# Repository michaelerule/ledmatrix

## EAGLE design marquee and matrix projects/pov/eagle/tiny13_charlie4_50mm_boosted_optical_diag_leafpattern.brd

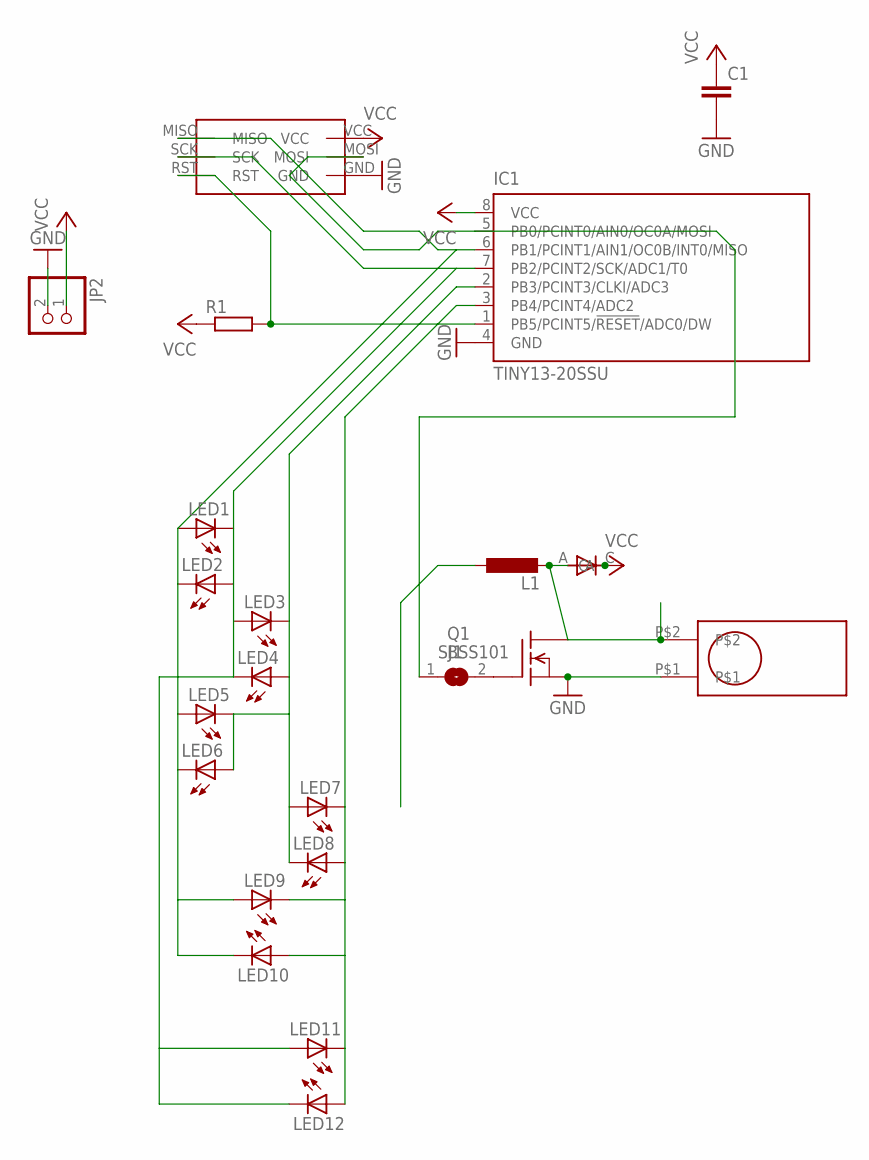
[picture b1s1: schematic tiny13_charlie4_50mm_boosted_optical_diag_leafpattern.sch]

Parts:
C1: C-EU025-025X050; C025-025X050
IC1: TINY13-20SSU; 8S1
JP2: PINHD-1X2; 1X02
L1: L-EU0204/5; 0204/5
LED1, LED2, LED3, LED4, LED5, LED6, LED7, LED8, LED9, LED10, LED11, LED12: LED3MM
Q1: BSS101; TO92
R1: R-EU_0204/5; 0204/5
SJ1: SJ
U$1: TILT_SWITCH_MECHANICAL
U$2: AVR_ISP_6_PIN_1X6_SMT_CONTACT_PROGRAMMER; CONTACT_ISP_PROGRAMMER_1X6_ATMEL_2
U$3: D-6; D-7.5

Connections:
GND: C1.2, IC1.4 (GND), JP2.2, Q1.1 (S), U$1.P$1, U$2.GND
unnamed: IC1.2 (PB3/PCINT3/CLKI/ADC3), LED3.K (C), LED4.A, LED5.K (C), LED6.A, LED7.A, LED8.K (C)
unnamed: IC1.7 (PB2/PCINT2/SCK/ADC1/T0), LED1.K (C), LED2.A, LED3.A, LED4.K (C), LED11.A, LED12.K (C), U$2.SCK
unnamed: L1.2, Q1.3 (D), U$1.P$2, U$3.A
unnamed: IC1.3 (PB4/PCINT4/ADC2), LED7.K (C), LED8.A, LED9.K (C), LED10.A, LED11.K (C), LED12.A
unnamed: IC1.5 (PB0/PCINT0/AIN0/OC0A/MOSI), SJ1.1, U$2.MOSI
unnamed: IC1.1 (PB5/PCINT5/!RESET!/ADC0/DW), R1.2, U$2.RST
unnamed: IC1.6 (PB1/PCINT1/AIN1/OC0B/INT0/MISO), LED1.A, LED2.K (C), LED5.A, LED6.K (C), LED9.A, LED10.K (C), U$2.MISO
unnamed: Q1.2 (G), SJ1.2
VCC: C1.1, IC1.8 (VCC), JP2.1, R1.1, U$2.VCC, U$3.C

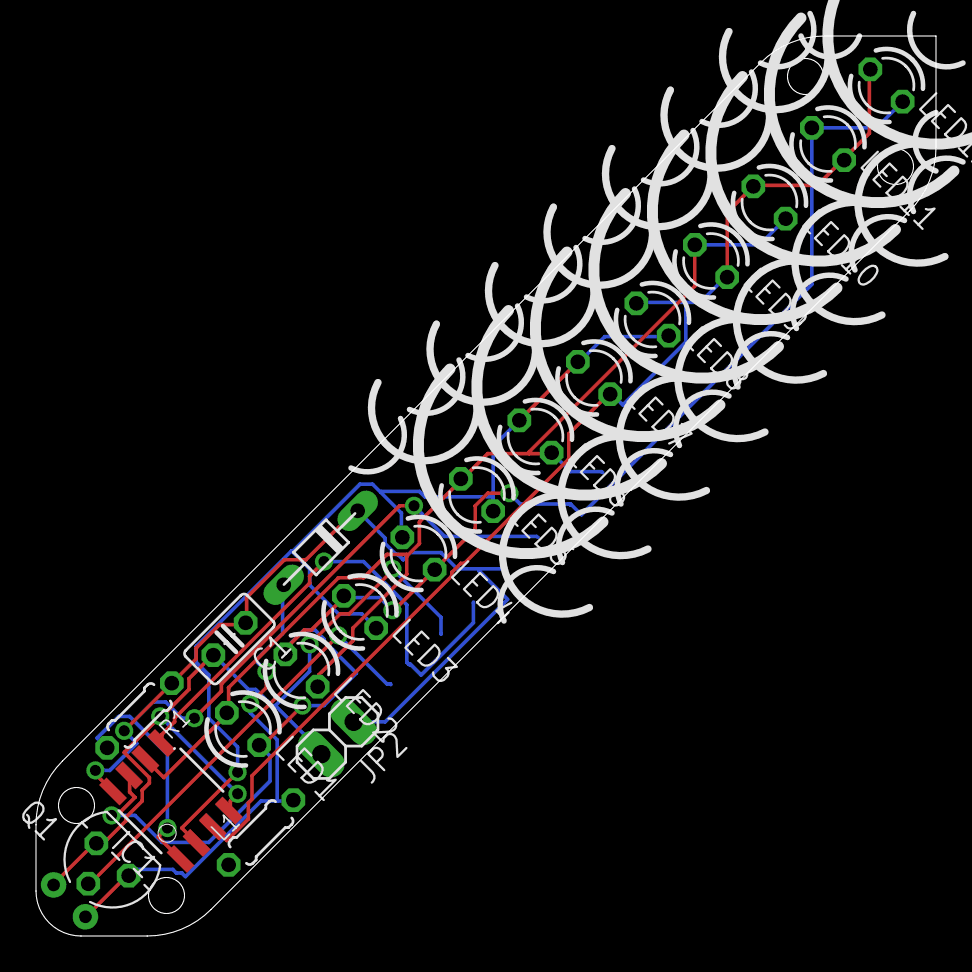
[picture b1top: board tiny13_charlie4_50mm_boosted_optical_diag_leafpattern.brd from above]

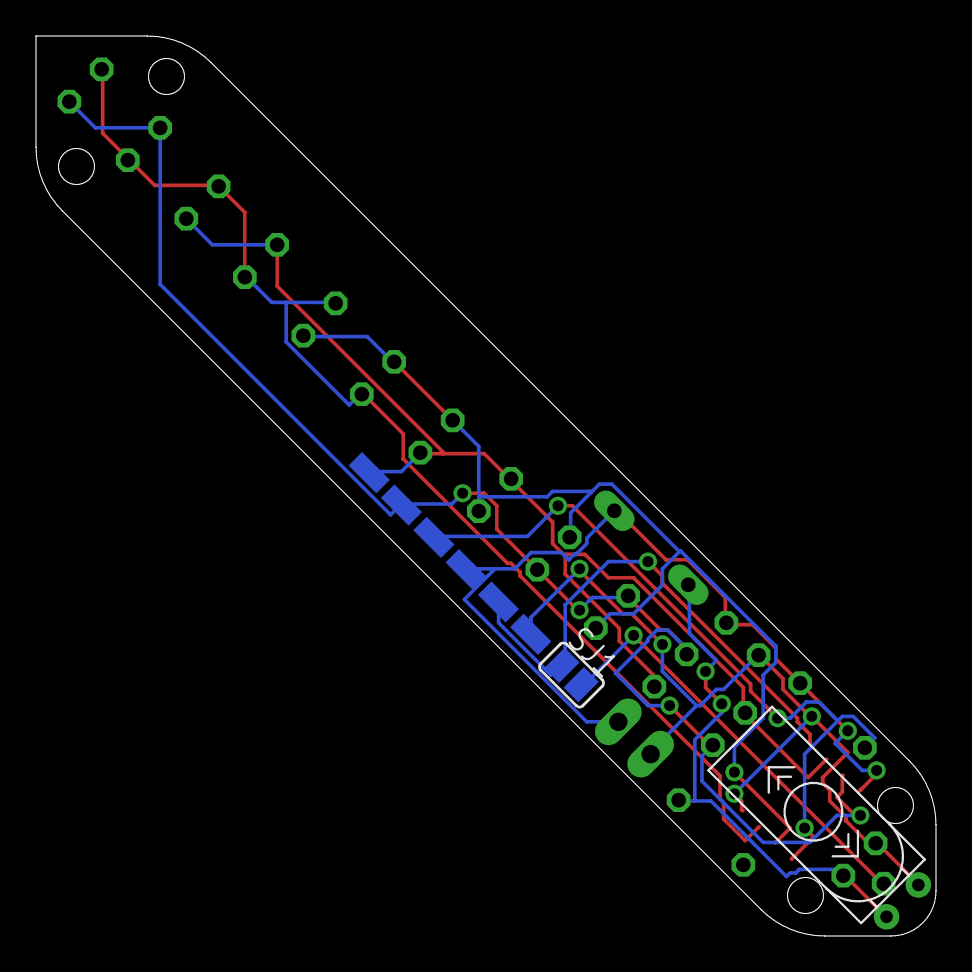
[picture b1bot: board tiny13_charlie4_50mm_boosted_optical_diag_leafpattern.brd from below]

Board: 2 copper layers, 50.0 x 50.0 mm, 22 parts (3 on the bottom side), 10 nets.

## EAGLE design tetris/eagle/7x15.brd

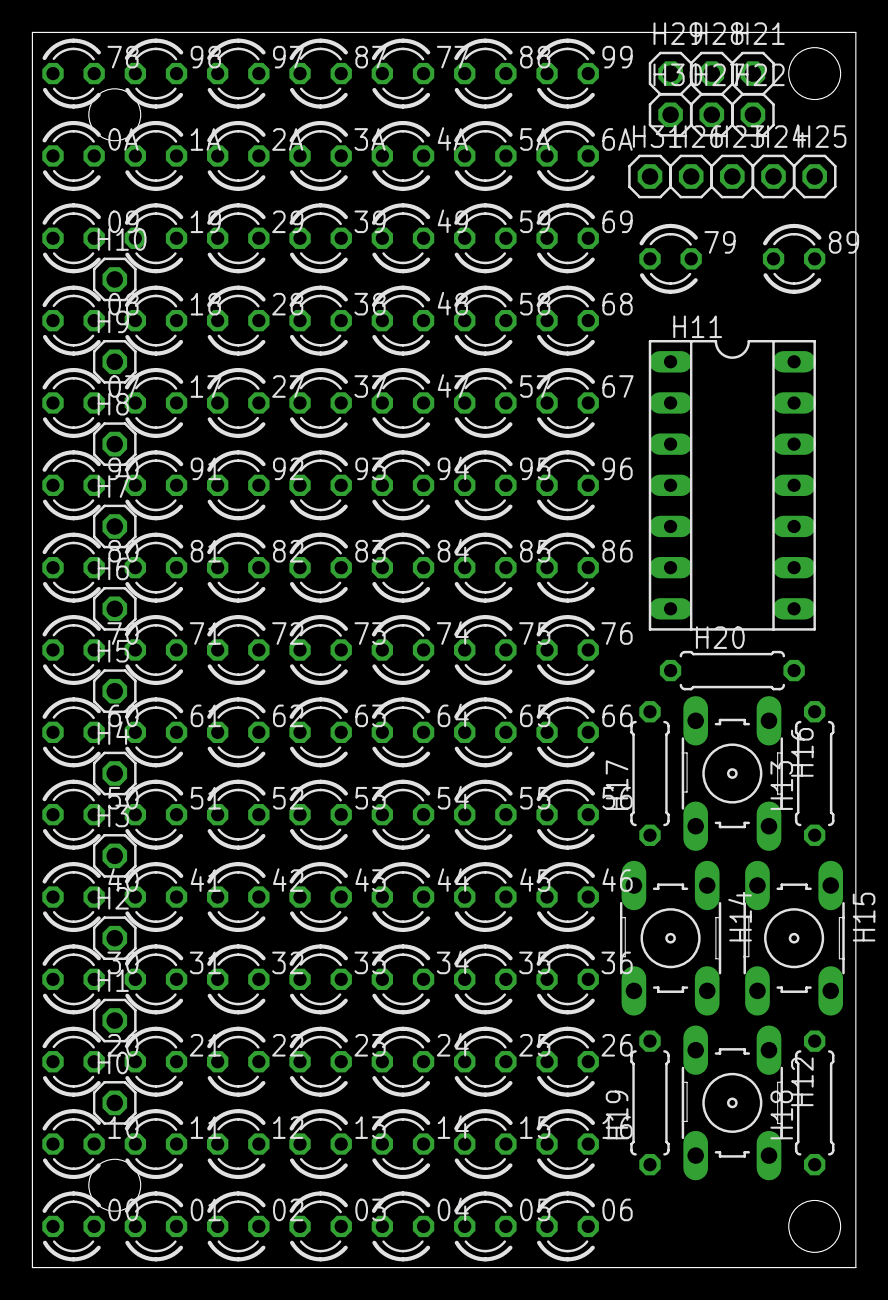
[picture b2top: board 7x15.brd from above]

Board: 2 copper layers, 50.8 x 76.2 mm, 139 parts (0 on the bottom side), 11 nets, no tracks yet.

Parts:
00, 0A, 01, 1A, 02, 2A, 03, 3A, 04, 4A, 05, 5A, 06, 6A, 07, 08, 09, 10, 11, 12, 13, 14, 15, 16, 17, 18, 19, 20, 21, 22, 23, 24, 25, 26, 27, 28, 29, 30, 31, 32, 33, 34, 35, 36, 37, 38, 39, 40, 41, 42, 43, 44, 45, 46, 47, 48, 49, 50, 51, 52, 53, 54, 55, 56, 57, 58, 59, 60, 61, 62, 63, 64, 65, 66, 67, 68, 69, 70, 71, 72, 73, 74, 75, 76, 77, 78, 79, 80, 81, 82, 83, 84, 85, 86, 87, 88, 89, 90, 91, 92, 93, 94, 95, 96, 97, 98, 99: LED3MM
H0, H1, H2, H3, H4, H5, H6, H7, H8, H9, H10, H21, H22, H23, H24, H25, H26, H27, H28, H29, H30, H31: 1X01
H11: SOCKET-14
H12, H14, H15, H16: B3F-10XX
H13, H17, H18, H19, H20: 0207/7

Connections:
D: 00.A, 0A.K, 1A.K, 2A.K, 3A.K, 4A.K, 5A.K, 6A.K, 11.A, 22.A, 33.A, 44.A, 55.A, 66.A, 77.A, 88.A, 99.A, H10.1
S0: 00.K, 0A.A, 01.A, 02.A, 03.A, 04.A, 05.A, 06.A, 07.A, 08.A, 09.A, 10.K, 20.K, 30.K, 40.K, 50.K, 60.K, 70.K, 80.K, 90.K, H0.1
S1: 01.K, 1A.A, 10.A, 11.K, 12.A, 13.A, 14.A, 15.A, 16.A, 17.A, 18.A, 19.A, 21.K, 31.K, 41.K, 51.K, 61.K, 71.K, 81.K, 91.K, H1.1
S2: 02.K, 2A.A, 12.K, 20.A, 21.A, 22.K, 23.A, 24.A, 25.A, 26.A, 27.A, 28.A, 29.A, 32.K, 42.K, 52.K, 62.K, 72.K, 82.K, 92.K, H2.1
S3: 03.K, 3A.A, 13.K, 23.K, 30.A, 31.A, 32.A, 33.K, 34.A, 35.A, 36.A, 37.A, 38.A, 39.A, 43.K, 53.K, 63.K, 73.K, 83.K, 93.K, H3.1
S4: 04.K, 4A.A, 14.K, 24.K, 34.K, 40.A, 41.A, 42.A, 43.A, 44.K, 45.A, 46.A, 47.A, 48.A, 49.A, 54.K, 64.K, 74.K, 84.K, 94.K, H4.1
S5: 05.K, 5A.A, 15.K, 25.K, 35.K, 45.K, 50.A, 51.A, 52.A, 53.A, 54.A, 55.K, 56.A, 57.A, 58.A, 59.A, 65.K, 75.K, 85.K, 95.K, H5.1
S6: 06.K, 6A.A, 16.K, 26.K, 36.K, 46.K, 56.K, 60.A, 61.A, 62.A, 63.A, 64.A, 65.A, 66.K, 67.A, 68.A, 69.A, 76.K, 86.K, 96.K, H6.1
S7: 07.K, 17.K, 27.K, 37.K, 47.K, 57.K, 67.K, 70.A, 71.A, 72.A, 73.A, 74.A, 75.A, 76.A, 77.K, 78.A, 87.K, 97.K, H7.1
S8: 08.K, 18.K, 28.K, 38.K, 48.K, 58.K, 68.K, 78.K, 80.A, 81.A, 82.A, 83.A, 84.A, 85.A, 86.A, 87.A, 88.K, 98.K, H8.1
S9: 09.K, 19.K, 29.K, 39.K, 49.K, 59.K, 69.K, 90.A, 91.A, 92.A, 93.A, 94.A, 95.A, 96.A, 97.A, 98.A, 99.K, H9.1

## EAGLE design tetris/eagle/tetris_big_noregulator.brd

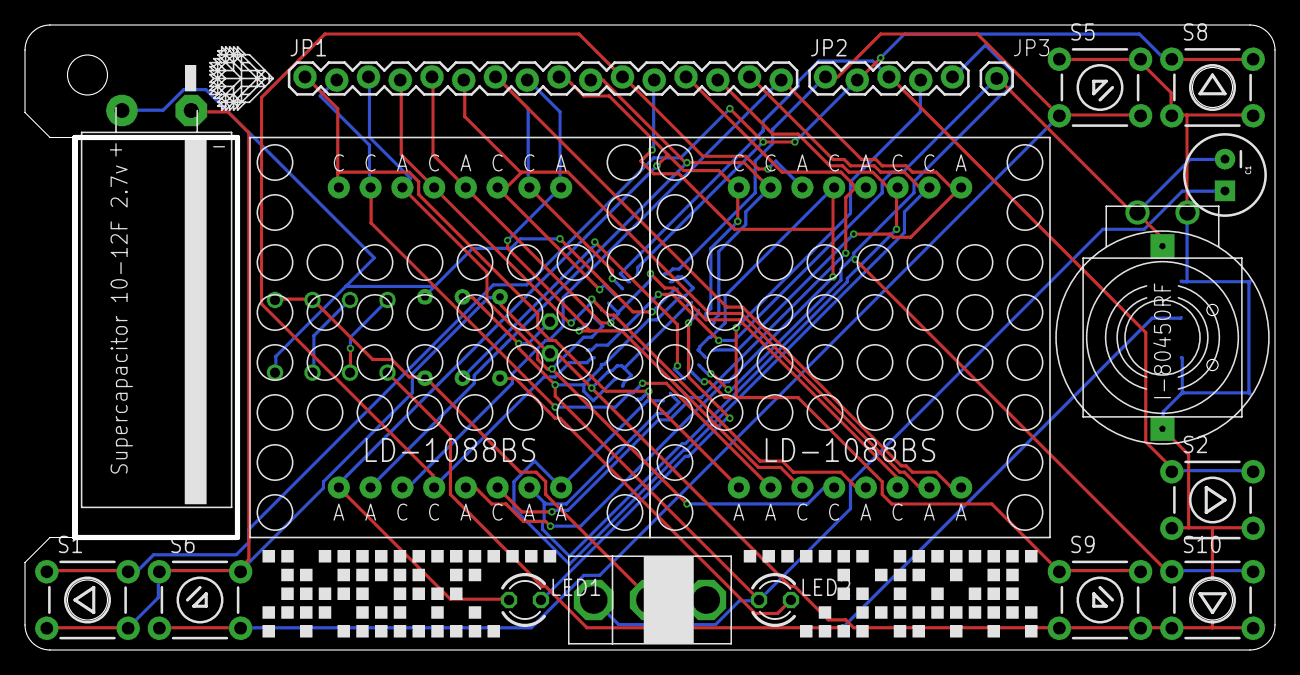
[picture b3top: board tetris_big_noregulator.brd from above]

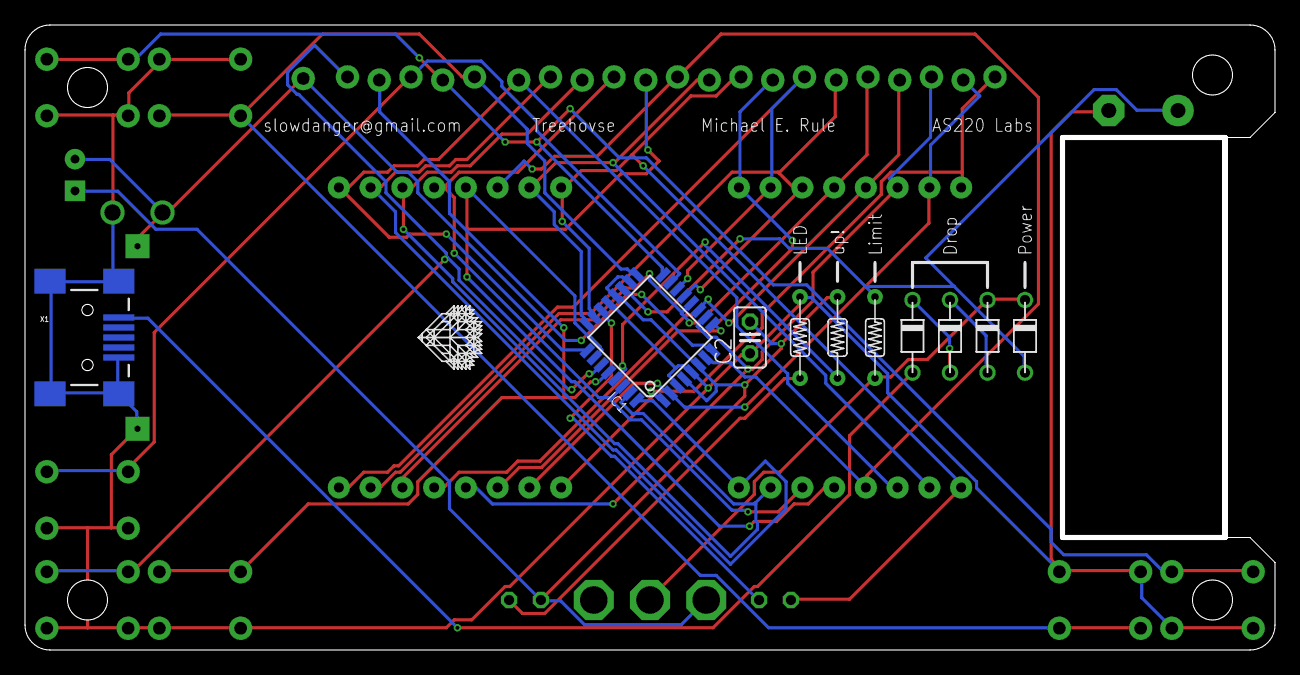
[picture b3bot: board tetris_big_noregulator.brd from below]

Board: 2 copper layers, 100.0 x 50.0 mm, 31 parts (11 on the bottom side), 32 nets.

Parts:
C1: CPOL-RADIAL-100UF-25V
C2: C025-025X050
IC1: MEGA8-AI; TQFP32-08
JP1: M16LOCK; 1X16_LOCK
JP2: 1X05_LOCK
JP3: M01PTH; 1X01
LED1, LED2: LED3MM
S1, S2, S5, S6, S8, S9, S10: TACTILE-PTH
U$1, U$2: LD-1088BS
U$3, U$6: LOGO
U$4: I-80450RF; ISK4.1K_I-80450RF_I2G
U$5: NICHICON_12F; NICHICON_10X30
U$7: PIEZO_ROUND_PTH; PIEZO_ROUND_ENCASED_PTH
U$8, U$10, U$11: R-7
U$9: SPST_BIG_PTH; SWITCH_BIG
U$13, U$14, U$15, U$16: D-6; D-7.5
X1: USB-MINIB-5PIN; USB-MINIB

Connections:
GND: C2.1, IC1.3, IC1.5, IC1.21, S1.3, S1.4, S2.3, S2.4, S5.1, S5.2, S6.1, S6.2, S8.3, S8.4, S9.3, S9.4, S10.3, S10.4, U$4.P$2, U$5.P$1, U$7.P$2, U$11.P$2, X1.GND, X1.MTN1, X1.MTN2, X1.MTN3, X1.MTN4
unnamed: IC1.32, JP1.15, U$1.A4, U$2.C1
unnamed: IC1.31, JP1.14, U$1.A5, U$2.C2
unnamed: IC1.30, JP1.13, U$1.C6, U$2.A2
unnamed: IC1.26, JP1.12, U$1.A6, U$2.C3
unnamed: IC1.7, JP1.11, U$1.C7, U$2.A3
unnamed: IC1.24, JP1.10, U$1.A7, U$2.C4
unnamed: IC1.23, JP1.9, LED1.A, U$1.A8, U$2.C5
unnamed: IC1.25, JP1.16, U$1.C8, U$2.A1
unnamed: U$15.A, X1.VBUS
unnamed: IC1.13, JP1.6, U$1.C2, U$2.A5
unnamed: IC1.12, JP1.5, U$1.A2, U$2.C6
unnamed: IC1.11, JP1.4, U$1.C3, U$2.A6
unnamed: IC1.10, JP1.3, U$1.A3, U$2.C7
unnamed: IC1.9, JP1.8, U$1.A1, U$2.C8
unnamed: IC1.2, JP1.2, U$1.C4, U$2.A7
unnamed: IC1.1, JP1.1, U$1.C5, U$2.A8
unnamed: C1.2, IC1.8, JP3.1, U$4.P$1, U$7.P$1
unnamed: U$14.A, U$15.C
unnamed: IC1.29, U$10.P$1
unnamed: IC1.27, JP2.5, S10.1, S10.2
unnamed: IC1.28, JP2.4, S9.1, S9.2
unnamed: IC1.15, JP2.3, S2.1, S2.2
unnamed: IC1.16, JP2.2, S1.1, S1.2, S8.1, S8.2
unnamed: U$8.P$2, U$9.P$2, U$13.C, U$16.C
unnamed: IC1.19, U$5.P$2, U$8.P$1, U$16.A
unnamed: IC1.17, JP2.1, S5.3, S5.4, S6.3, S6.4
unnamed: U$13.A, U$14.C
unnamed: IC1.14, JP1.7, U$1.C1, U$2.A4
unnamed: LED2.K, U$11.P$1
unnamed: IC1.22, LED1.K
VCC: C1.1, C2.2, IC1.4, IC1.6, IC1.18, IC1.20, LED2.A, U$9.P$1, U$10.P$2

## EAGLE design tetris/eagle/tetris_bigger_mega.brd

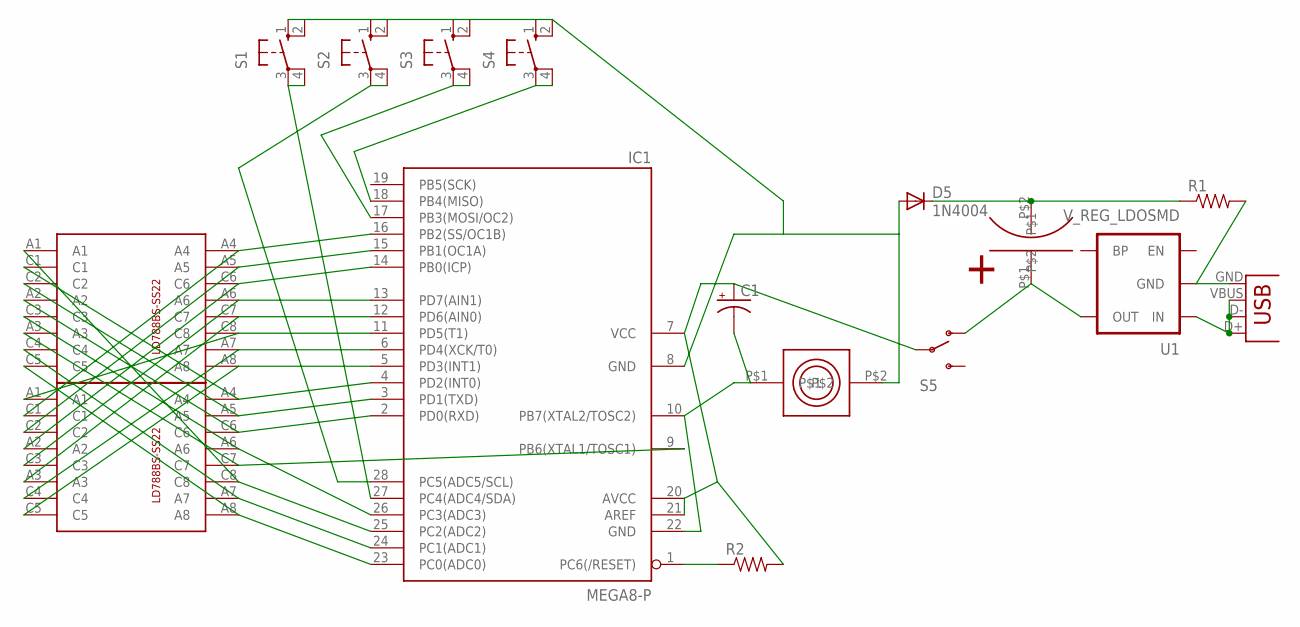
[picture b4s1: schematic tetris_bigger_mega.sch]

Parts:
C1: CAP_POLPTH1; CPOL-RADIAL-100UF-25V
D5: 1N4004; DO41-10
IC1: MEGA8-P; DIL28-3
R1, R2: RESISTORPTH1; AXIAL-0.3
S1, S2, S3, S4: 10-XX; B3F-10XX
S5: SWITCH-SPSTSMD2; SWITCH-SPDT-SMD
U1: V_REG_LDOSMD; SOT23-5
U$1, U$2: LD-1088BS
U$4: I-80450RF; ISK4.1K_I-80450RF_I2G
U$5: NICHICON_12F; NICHICON_10X30
X1: USB-MICROB

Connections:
unnamed: IC1.4 (PD2(INT0)), U$1.A4, U$2.C1
unnamed: IC1.3 (PD1(TXD)), U$1.A5, U$2.C2
unnamed: IC1.2 (PD0(RXD)), U$1.C6, U$2.A2
unnamed: IC1.26 (PC3(ADC3)), U$1.A6, U$2.C3
unnamed: IC1.9 (PB6(XTAL1/TOSC1)), U$1.C7, U$2.A3
unnamed: IC1.24 (PC1(ADC1)), U$1.A7, U$2.C4
unnamed: IC1.23 (PC0(ADC0)), U$1.A8, U$2.C5
unnamed: IC1.25 (PC2(ADC2)), U$1.C8, U$2.A1
unnamed: D5.C, R1.P$1 (1), U$5.P$2
unnamed: IC1.15 (PB1(OC1A)), U$1.C2, U$2.A5
unnamed: IC1.14 (PB0(ICP)), U$1.A2, U$2.C6
unnamed: IC1.13 (PD7(AIN1)), U$1.C3, U$2.A6
unnamed: IC1.12 (PD6(AIN0)), U$1.A3, U$2.C7
unnamed: IC1.11 (PD5(T1)), U$1.A1, U$2.C8
unnamed: IC1.6 (PD4(XCK/T0)), U$1.C4, U$2.A7
unnamed: IC1.5 (PD3(INT1)), U$1.C5, U$2.A8
unnamed: C1.2 (-), IC1.10 (PB7(XTAL2/TOSC2)), IC1.22 (GND), U$4.P$1
unnamed: S5.1 (O), U1.5 (OUT), U$5.P$1
unnamed: IC1.27 (PC4(ADC4/SDA)), S1.3, S1.4 (P1)
unnamed: IC1.28 (PC5(ADC5/SCL)), S2.3, S2.4 (P1)
unnamed: IC1.17 (PB3(MOSI/OC2)), S3.3, S3.4 (P1)
unnamed: IC1.18 (PB4(MISO)), S4.3, S4.4 (P1)
unnamed: R1.P$2 (2), U1.2 (GND), X1.GND
unnamed: U1.1 (IN), X1.D+, X1.D-, X1.VBUS
unnamed: C1.1 (+), IC1.7 (VCC), IC1.20 (AVCC), IC1.21 (AREF), R2.P$2 (2), S5.2
unnamed: D5.A, IC1.8 (GND), S1.1 (S), S1.2 (S1), S2.1 (S), S2.2 (S1), S3.1 (S), S3.2 (S1), S4.1 (S), S4.2 (S1), U$4.P$2
unnamed: IC1.16 (PB2(SS/OC1B)), U$1.C1, U$2.A4
unnamed: IC1.1 (PC6(/RESET)), R2.P$1 (1)

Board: 2 copper layers, 16 parts (0 on the bottom side), 28 nets, no tracks yet.

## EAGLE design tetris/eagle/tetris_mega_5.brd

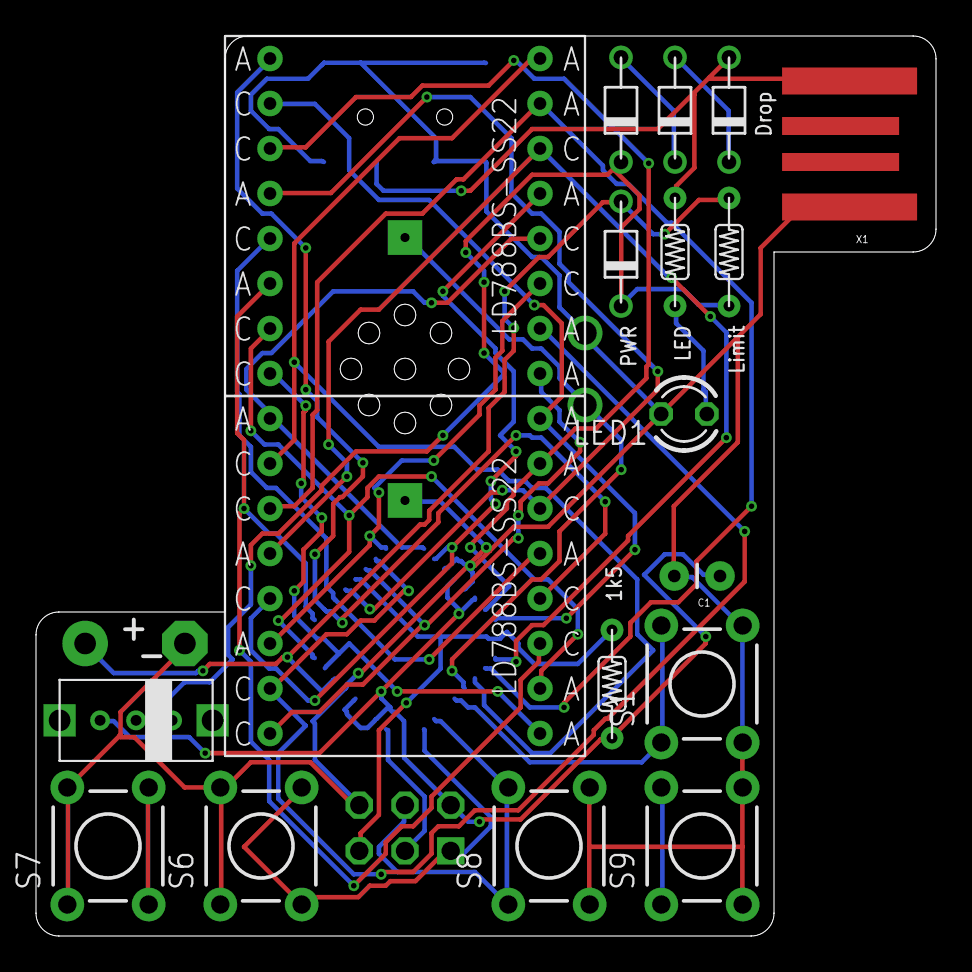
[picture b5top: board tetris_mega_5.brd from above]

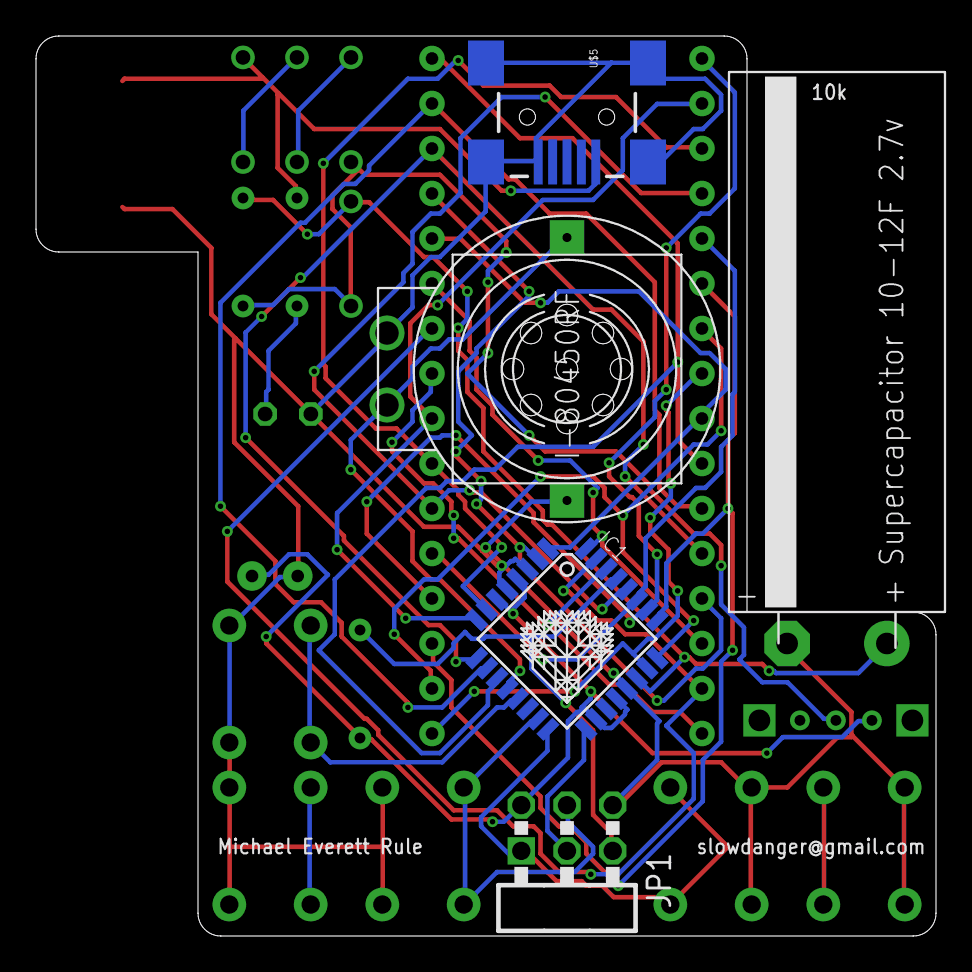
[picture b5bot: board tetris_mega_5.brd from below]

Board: 2 copper layers, 50.0 x 50.0 mm, 25 parts (7 on the bottom side), 32 nets.

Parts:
C1: CAP-PTH-SMALL
IC1: MEGA8-AI; TQFP32-08
JP1: AVR-ISP-6R
LED1: LED3MM
S1, S6, S7, S8, S9: TACTILE-PTH
U$1, U$2: LD788BS-SS22
U$3: PIEZO_ROUND_PTH; PIEZO_ROUND_ENCASED_PTH
U$4: I-80450RF; ISK4.1K_I-80450RF_I2G
U$5: USB-MINIB-5PIN; USB-MINIB
U$6: NICHICON_12F; NICHICON_10X30
U$7, U$11, U$17: R-6
U$8, U$9, U$10, U$12: D-6; D-7.5
U$13: LOGO
U$15: SPST_PTH; SWITCH2
X1: USBPCB; USB-A-PCB

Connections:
GND: C1.2, IC1.3, IC1.5, IC1.21, JP1.6, LED1.K, S1.3, S1.4, S6.1, S6.2, S7.1, S7.2, S8.3, S8.4, S9.3, S9.4, U$3.P$2, U$4.P$2, U$5.GND, U$5.MTN1, U$5.MTN2, U$5.MTN3, U$5.MTN4, U$6.P$1, X1.GND
unnamed: IC1.23, U$1.A8, U$2.C5
unnamed: IC1.24, U$1.A7, U$2.C4
unnamed: IC1.25, U$1.C8, U$2.A3
unnamed: IC1.30, U$1.C5, U$2.A8
unnamed: IC1.31, U$1.C4, U$2.A7
unnamed: IC1.32, U$1.A3, U$2.C8
unnamed: IC1.8, U$1.A4, U$2.C1
unnamed: IC1.7, U$1.A5, U$2.C2
unnamed: IC1.28, U$1.C6, U$2.A2
unnamed: IC1.27, U$1.A6, U$2.C3
unnamed: IC1.11, U$1.C1, U$2.A4
unnamed: IC1.10, U$1.C2, U$2.A5
unnamed: IC1.9, U$1.A2, U$2.C6
unnamed: IC1.2, U$1.C3, U$2.A6
unnamed: IC1.1, U$1.A1, U$2.C7
unnamed: IC1.26, U$1.C7, U$2.A1
unnamed: IC1.29, JP1.5, U$7.P$1
unnamed: U$8.C, U$9.A
unnamed: U$9.C, U$10.A
unnamed: IC1.17, JP1.3
unnamed: IC1.16, JP1.1, S6.3, S6.4
unnamed: U$5.VBUS, U$8.A, U$17.P$1, X1.5V
unnamed: S9.1, S9.2
unnamed: S7.3, S7.4
unnamed: IC1.13, S1.1, S1.2
unnamed: IC1.12, U$3.P$1, U$4.P$1
unnamed: U$10.C, U$11.P$2, U$12.C, U$15.2
unnamed: IC1.22, U$6.P$2, U$11.P$1, U$12.A
unnamed: LED1.A, U$17.P$2
unnamed: IC1.15, JP1.4, S8.1, S8.2
VCC: C1.1, IC1.4, IC1.6, IC1.18, IC1.20, JP1.2, U$7.P$2, U$15.1

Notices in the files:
parts and their libraries:
SparkFun-Electromechanical: Licensing: CC v3.0 Share-Alike You are welcome to use this library for commercial purposes.
